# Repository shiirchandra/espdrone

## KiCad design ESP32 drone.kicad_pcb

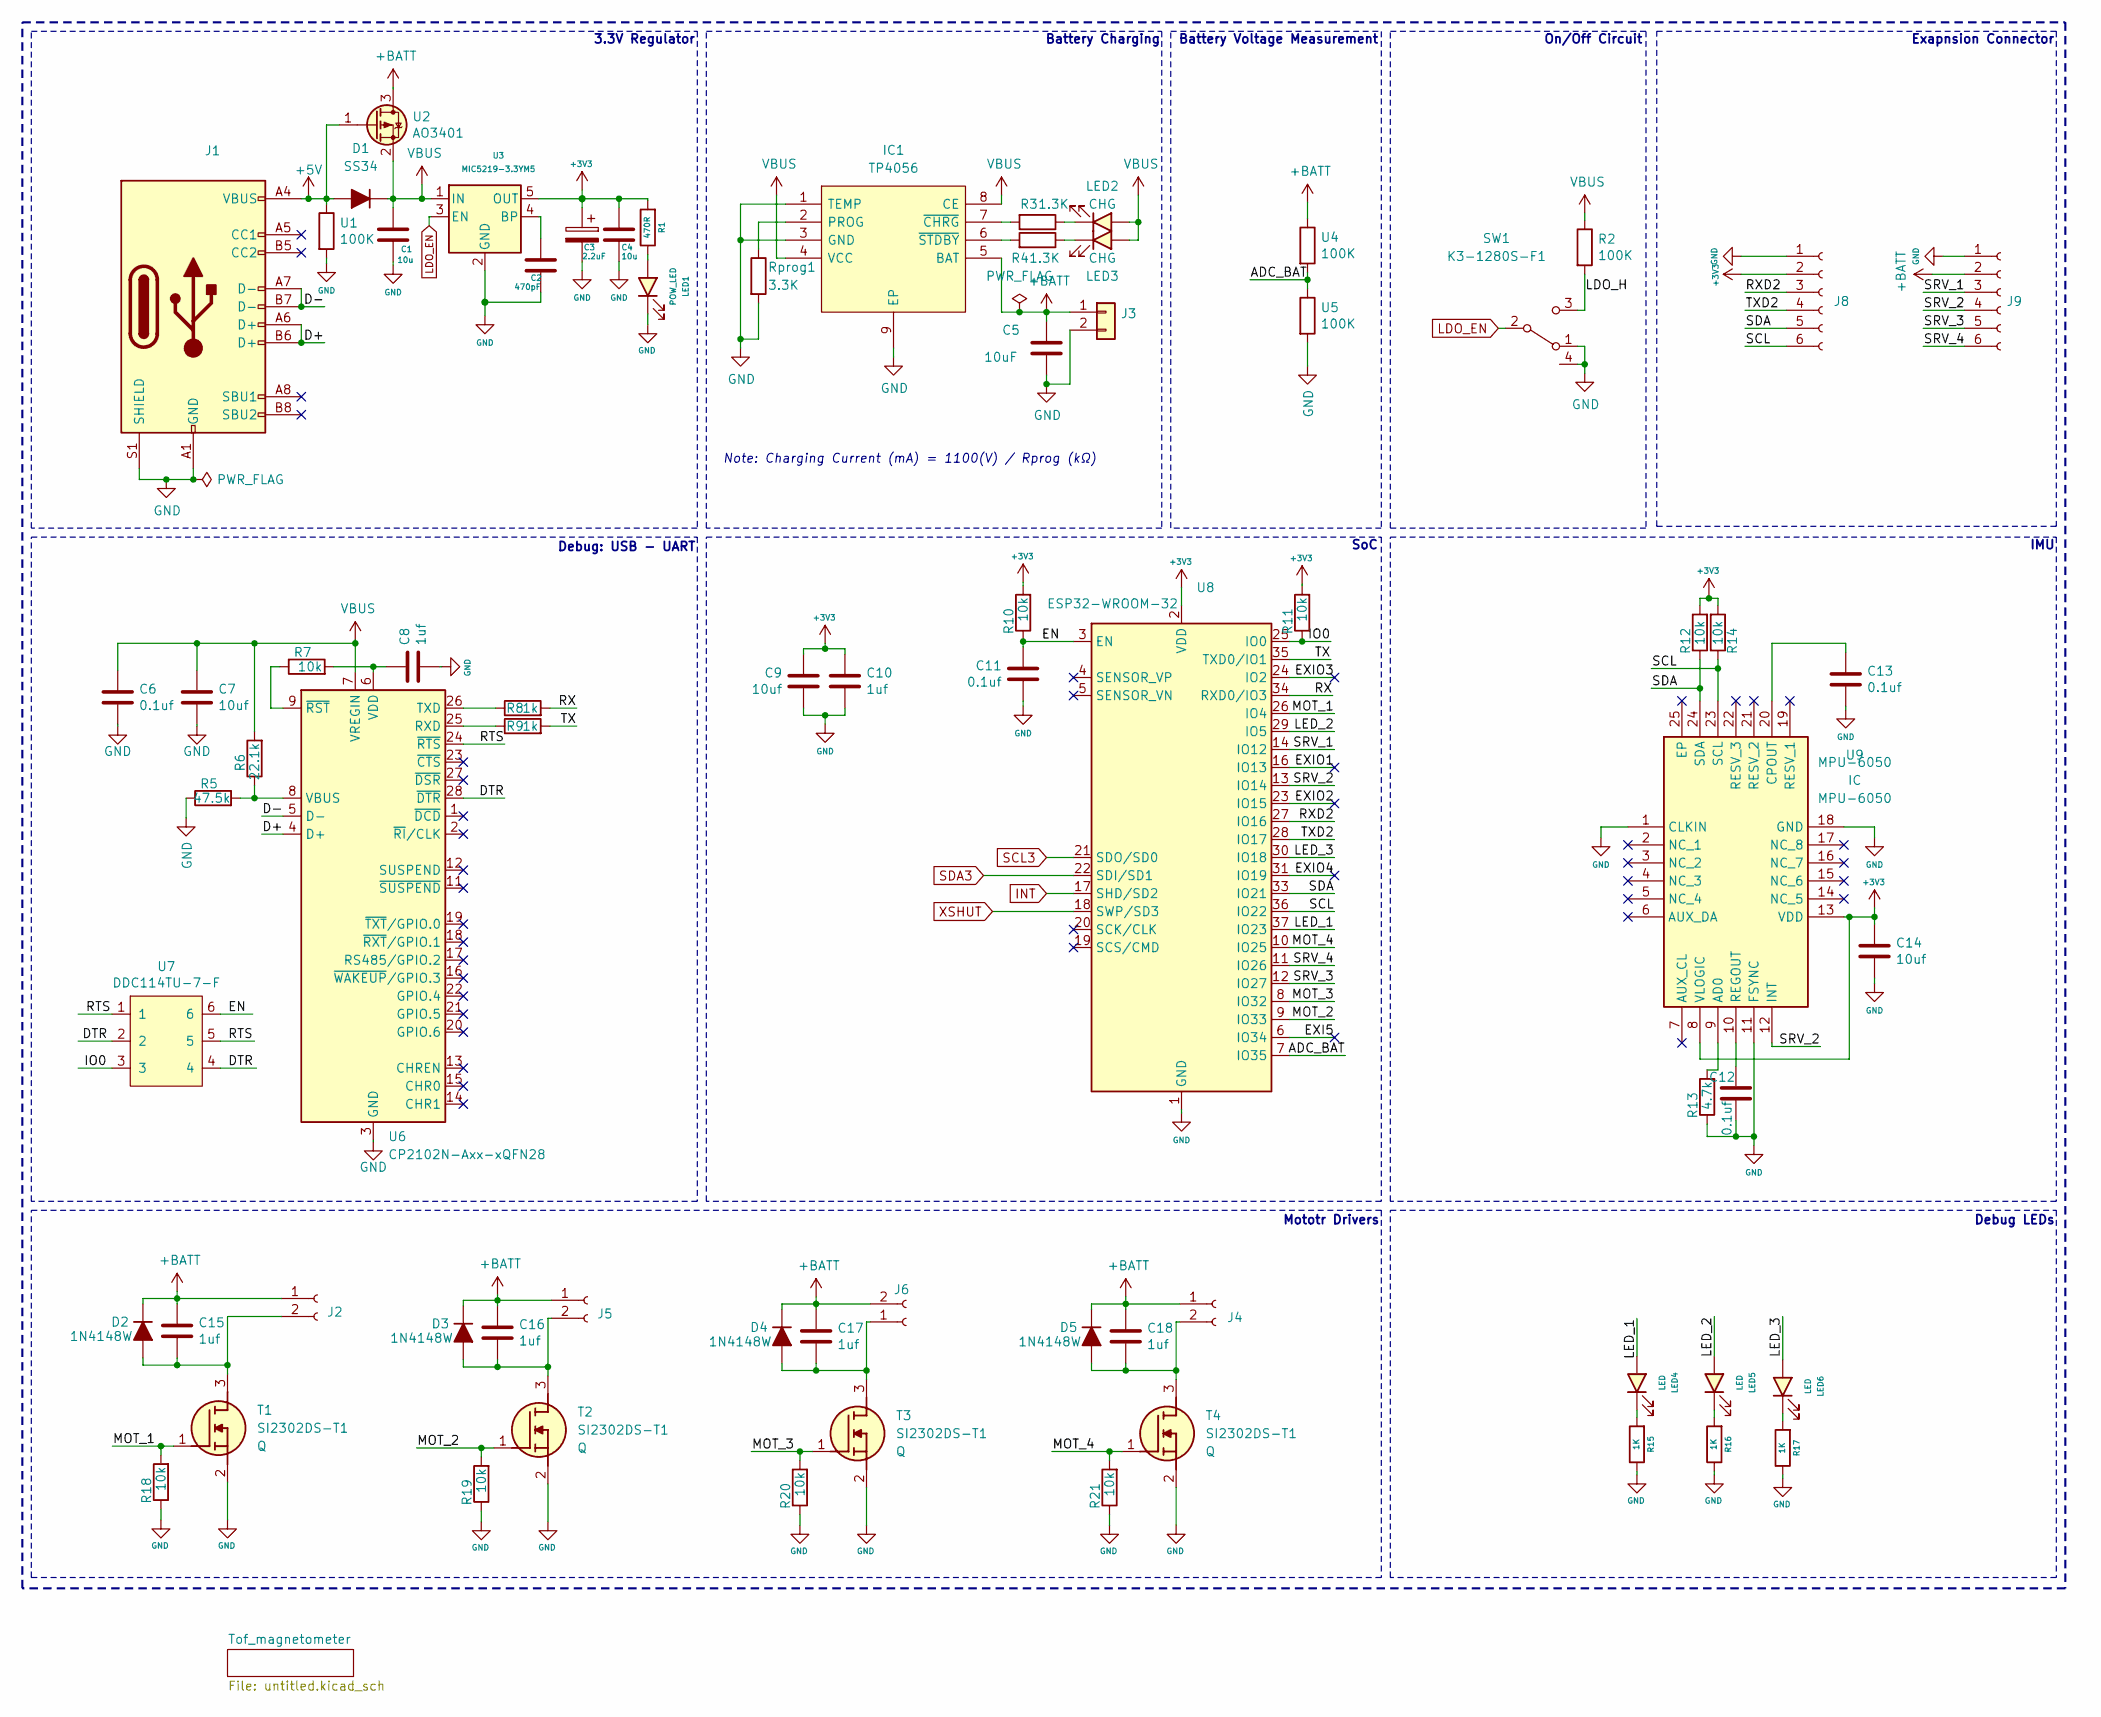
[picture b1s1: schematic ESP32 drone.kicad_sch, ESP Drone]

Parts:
C1, C4: 10u; C_0603_1608Metric
C2: 470pF; C_0603_1608Metric
C3: 2.2uF; C_0805_2012Metric
C5: 10uF; C_0603_1608Metric
C6, C11, C12, C13: 0.1uf; C_0603_1608Metric
C7, C9, C14: 10uf; C_0603_1608Metric
C8, C10, C15, C16, C17, C18: 1uf; C_0603_1608Metric
D1: SS34; D_SMA
D2, D3, D4, D5: 1N4148W; D_SOD-323
IC1: TP4056; SOIC-8-1EP_3.9x4.9mm_P1.27mm_EP2.29x3mm; Manufacturer_Part_Number TP4056-42-ESOP8
J1: USB_C_Receptacle_USB2.0; USB_C_Receptacle_HRO_TYPE-C-31-M-12
J2, J4, J5, J6: Conn_01x02_Female; JST_GH_SM02B-GHS-TB_1x02-1MP_P1.25mm_Horizontal
J3: B2B-PH-SM4-TB(LF)(SN); JST_PH_B2B-PH-SM4-TB_1x02-1MP_P2.00mm_Vertical
J8, J9: Conn_01x06_Female; PinHeader_1x06_P2.54mm_Vertical
LED1: POW_LED; LED_0603_1608Metric
LED2, LED3: CHG; LED_0603_1608Metric
LED4, LED5, LED6: LED; LED_0603_1608Metric
R1: 470R; R_0603_1608Metric
R2: 100K; R_0603_1608Metric
R3, R4: 1.3K; R_0603_1608Metric
R5: 47.5k; R_0603_1608Metric
R6: 22.1k; R_0603_1608Metric
R7, R10, R11, R12, R14, R18, R19, R20, R21: 10k; R_0603_1608Metric
R8, R9: 1k; R_0603_1608Metric
R13: 4.7k; R_0603_1608Metric
R15, R16, R17: 1K; R_0603_1608Metric
Rprog1: 3.3K; R_0603_1608Metric
SW1: K3-1280S-F1; slide switch spdt
T1, T2, T3, T4: SI2302DS-T1; SOT-23; Mouser Part Number 781-SI2302DS
U1, U4, U5: 100K; R_0603_1608Metric
U2: AO3401; SOT-23
U3: MIC5219-3.3YM5; SOT-23-5
U6: CP2102N-Axx-xQFN28; QFN-28-1EP_5x5mm_P0.5mm_EP3.35x3.35mm
U7: DDC114TU-7-F; SOT-363_SC-70-6
U8: ESP32-WROOM-32
U9: MPU-6050; MPU6050; Mouser Part Number 410-MPU-6050

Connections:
+3V3: C3.1, C4.1, C9.1, C10.1, C14.1, J8.2, R1.2, R10.2, R11.2, R12.2, R14.2, U3.5 (OUT), U8.2 (VDD), U9.8 (VLOGIC), U9.13 (VDD); also elsewhere on the board
+5V: D1.2 (A), J1.A4 (VBUS), J1.A9 (VBUS), J1.B4 (VBUS), J1.B9 (VBUS), U1.1, U2.1 (G)
+BATT: C5.1, C15.1, C16.1, C17.1, C18.1, D2.1 (K), D3.1 (K), D4.1 (K), D5.1 (K), IC1.5 (BAT), J2.1, J3.1, J4.1, J5.1, J6.2, J9.2, U2.3 (D), U4.1
/ADC_BAT: U4.2, U5.1, U8.7 (IO35)
/D+: J1.A6 (D+), J1.B6 (D+), U6.4 (D+)
/D-: J1.A7 (D-), J1.B7 (D-), U6.5 (D-)
/DTR: U6.28 (~DTR), U7.2, U7.4
/EN: C11.1, R10.1, U7.6, U8.3 (EN)
/EXI5: U8.6 (IO34)
/EXIO1: U8.16 (IO13)
/EXIO2: U8.23 (IO15)
/EXIO3: U8.24 (IO2)
/EXIO4: U8.31 (IO19)
/IO0: R11.1, U7.3, U8.25 (IO0)
/LDO_H: R2.2, SW1.3 (C)
/LED_1: LED4.2 (A), U8.37 (IO23)
/LED_2: LED5.2 (A), U8.29 (IO5)
/LED_3: LED6.2 (A), U8.30 (IO18)
/MOT_1: R18.2, T1.1 (G), U8.26 (IO4)
/MOT_2: R19.2, T2.1 (G), U8.9 (IO33)
/MOT_3: R20.2, T3.1 (G), U8.8 (IO32)
/MOT_4: R21.2, T4.1 (G), U8.10 (IO25)
/RTS: U6.24 (~RTS), U7.1, U7.5
/RX: R8.2, U8.34 (RXD0/IO3)
/RXD2: J8.3, U8.27 (IO16)
/SCL: J8.6, R14.1, U8.36 (IO22), U9.23 (SCL)
/SDA: J8.5, R12.1, U8.33 (IO21), U9.24 (SDA)
/SRV_1: J9.3, U8.14 (IO12)
/SRV_2: J9.4, U8.13 (IO14), U9.12 (INT)
/SRV_3: J9.5, U8.12 (IO27)
/SRV_4: J9.6, U8.11 (IO26)
/TX: R9.2, U8.35 (TXD0/IO1)
/TXD2: J8.4, U8.28 (IO17)
GND: C1.2, C2.2, C3.2, C4.2, C5.2, C6.2, C7.2, C8.2, C9.2, C10.2, C11.2, C12.2, C13.2, C14.2, IC1.1 (TEMP), IC1.3 (GND), IC1.9 (EP), J1.A1 (GND), J1.A12 (GND), J1.B1 (GND), J1.B12 (GND), J1.S1 (SHIELD), J3.2, J8.1, J9.1, LED1.1 (K), R5.1, R13.1, R15.1, R16.1, R17.1, R18.1, R19.1, R20.1, R21.1, Rprog1.2, SW1.1 (A), SW1.4, T1.2 (S), T2.2 (S), T3.2 (S), T4.2 (S), U1.2, U3.2 (GND), U5.2, U6.3 (GND), U6.29 (GND), U8.1 (GND), U8.15 (GND), U8.38 (GND), U8.39 (GND), U9.1 (CLKIN), U9.11 (FSYNC), U9.18 (GND); also elsewhere on the board
INT: U8.17 (SHD/SD2); also elsewhere on the board
LDO_EN: SW1.2 (B), U3.3 (EN)
unnamed: C15.2, D2.2 (A), J2.2, T1.3 (D)
unnamed: C16.2, D3.2 (A), J5.2, T2.3 (D)
unnamed: C17.2, D4.2 (A), J6.1, T3.3 (D)
unnamed: C18.2, D5.2 (A), J4.2, T4.3 (D)
unnamed: IC1.2 (PROG), Rprog1.1
unnamed: IC1.7 (~CHRG), R3.2
unnamed: IC1.6 (~STDBY), R4.2
unnamed: LED1.2 (A), R1.1
unnamed: LED2.1 (K), R3.1
unnamed: LED3.1 (K), R4.1
unnamed: LED4.1 (K), R15.2
unnamed: LED5.1 (K), R16.2
unnamed: LED6.1 (K), R17.2
unnamed: C2.1, U3.4 (BP)
unnamed: R9.1, U6.25 (RXD)
unnamed: R8.1, U6.26 (TXD)
unnamed: R5.2, R6.1, U6.8 (VBUS)
unnamed: C8.1, R7.2, U6.6 (VDD)
unnamed: R7.1, U6.9 (~RST)
unnamed: R13.2, U9.9 (AD0)
unnamed: C13.1, U9.20 (CPOUT)
unnamed: C12.1, U9.10 (REGOUT)
SCL3: U8.21 (SDO/SD0); also elsewhere on the board
SDA3: U8.22 (SDI/SD1); also elsewhere on the board
VBUS: C1.1, C6.1, C7.1, D1.1 (K), IC1.4 (VCC), IC1.8 (CE), LED2.2 (A), LED3.2 (A), R2.1, R6.2, U2.2 (S), U3.1 (IN), U6.7 (VREGIN)
XSHUT: U8.18 (SWP/SD3); also elsewhere on the board

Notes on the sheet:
SoC
Battery Voltage Measurement
IMU
Mototr Drivers
Battery Charging
Debug LEDs
Debug: USB - UART
Exapnsion Connector
3.3V Regulator
Note: Charging Current (mA) = 1100(V) / Rprog (kΩ)
On/Off Circuit

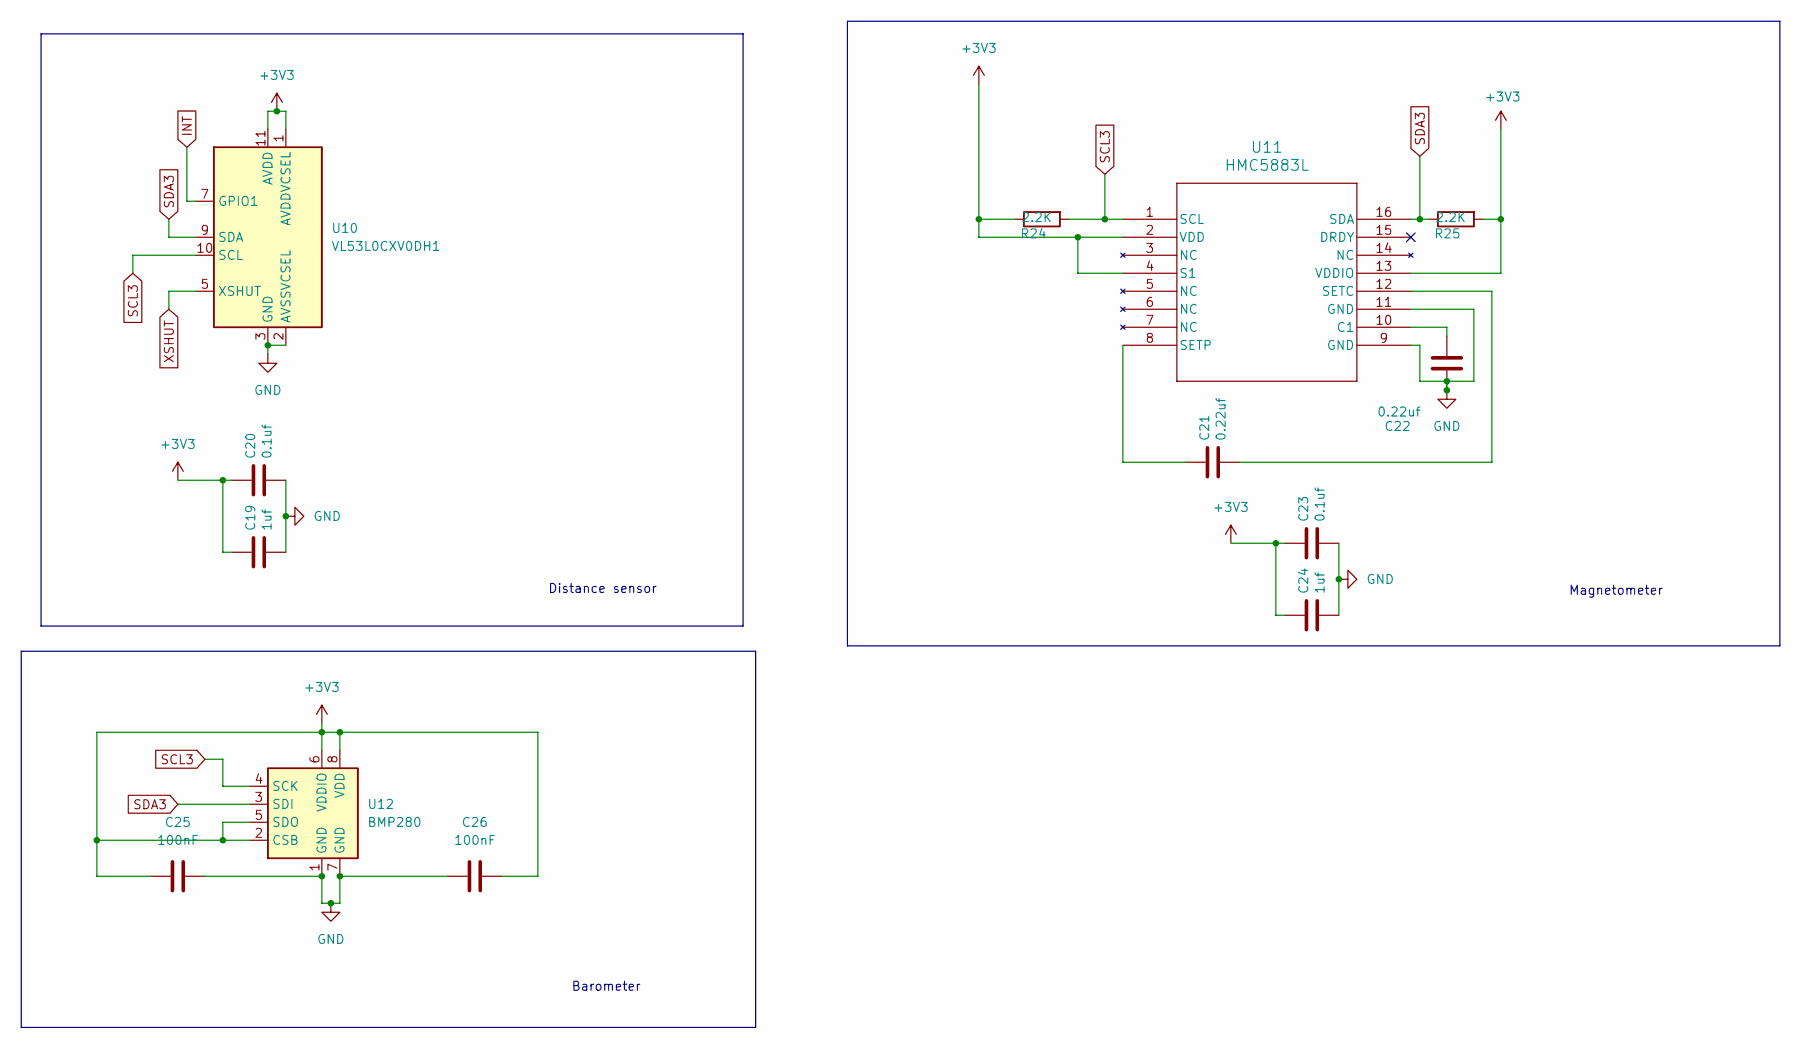
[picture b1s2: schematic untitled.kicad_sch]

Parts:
C19, C24: 1uf; C_0603_1608Metric
C20, C23: 0.1uf; C_0603_1608Metric
C21, C22: 0.22uf; C_0603_1608Metric
C25, C26: 100nF; C_0603_1608Metric
R24, R25: 2.2K; R_0603_1608Metric
U10: VL53L0CXV0DH1; ST_VL53L1x
U11: HMC5883L; LPCC16_HNW
U12: BMP280; Bosch_LGA-8_2x2.5mm_P0.65mm_ClockwisePinNumbering

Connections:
+3V3: C19.1, C20.1, C23.1, C24.1, C25.1, C26.2, R24.1, R25.2, U10.1 (AVDDVCSEL), U10.11 (AVDD), U11.2 (VDD), U11.4 (S1), U11.13 (VDDIO), U12.2 (CSB), U12.5 (SDO), U12.6 (VDDIO), U12.8 (VDD); also elsewhere on the board
GND: C19.2, C20.2, C22.2, C23.2, C24.2, C25.2, C26.1, U10.2 (AVSSVCSEL), U10.3 (GND), U10.4 (GND), U10.6 (GND), U10.12 (GND), U11.9 (GND), U11.11 (GND), U12.1 (GND), U12.7 (GND); also elsewhere on the board
INT: U10.7 (GPIO1); also elsewhere on the board
unnamed: C22.1, U11.10 (C1)
unnamed: C21.2, U11.12 (SETC)
unnamed: C21.1, U11.8 (SETP)
SCL3: R24.2, U10.10 (SCL), U11.1 (SCL), U12.4 (SCK); also elsewhere on the board
SDA3: R25.1, U10.9 (SDA), U11.16 (SDA), U12.3 (SDI); also elsewhere on the board
XSHUT: U10.5 (XSHUT); also elsewhere on the board

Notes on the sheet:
Magnetometer
Distance sensor
Barometer

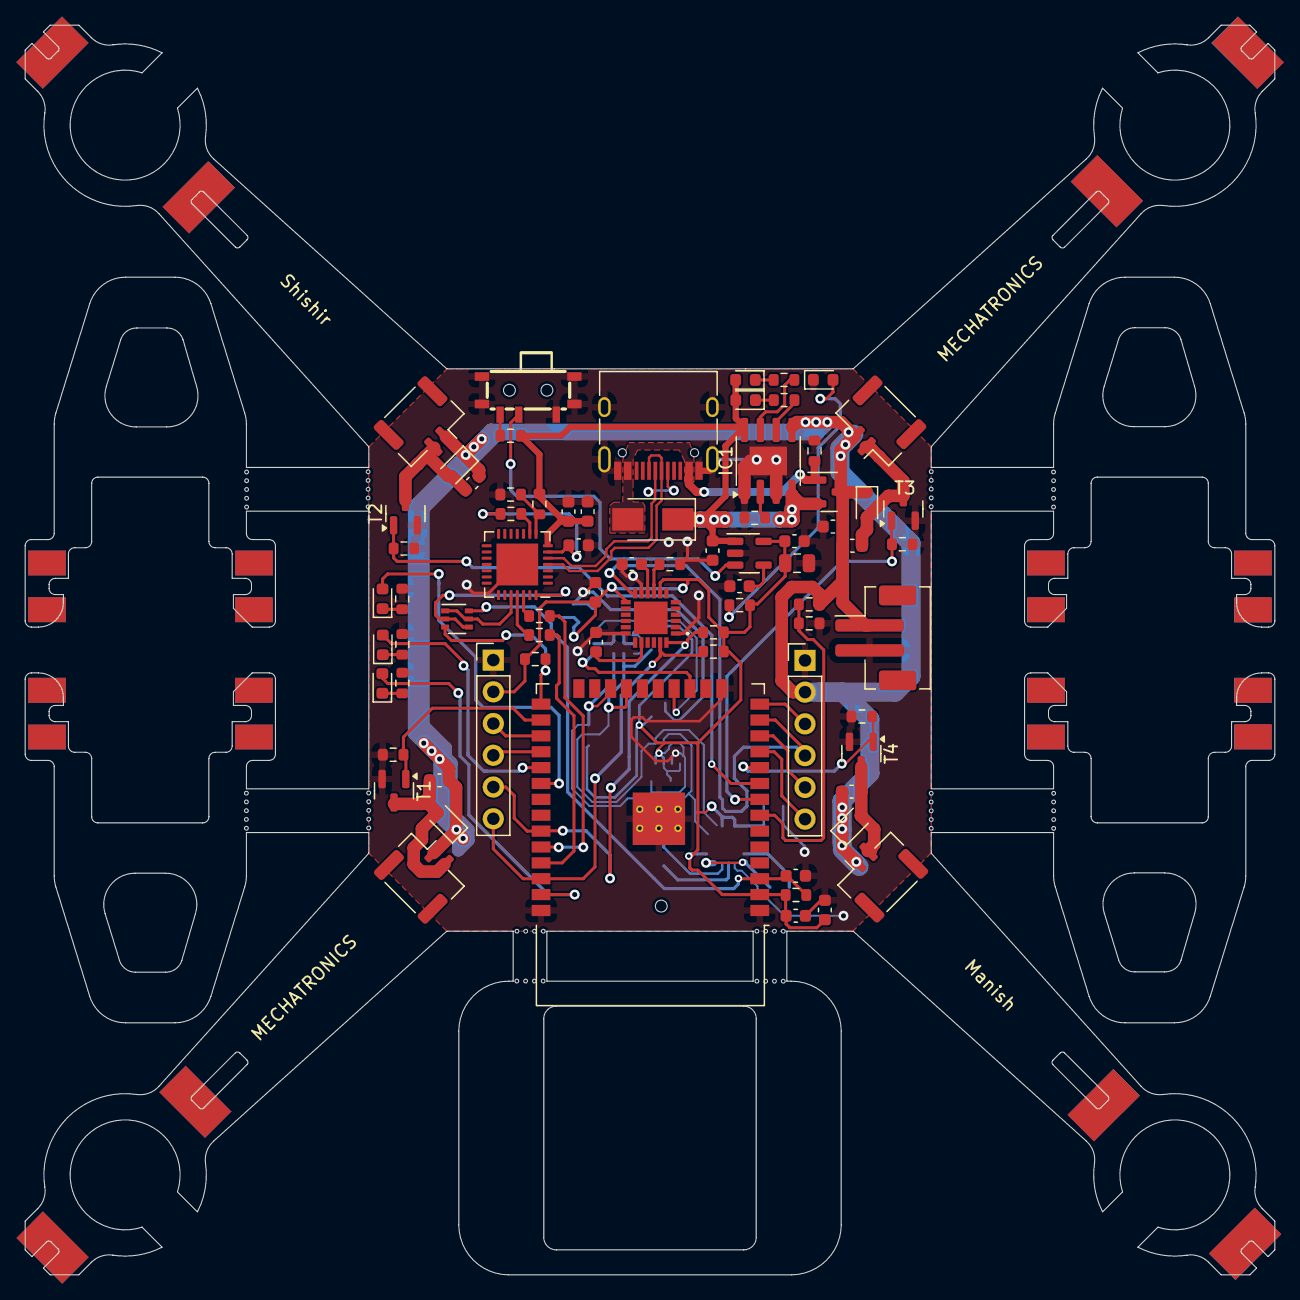
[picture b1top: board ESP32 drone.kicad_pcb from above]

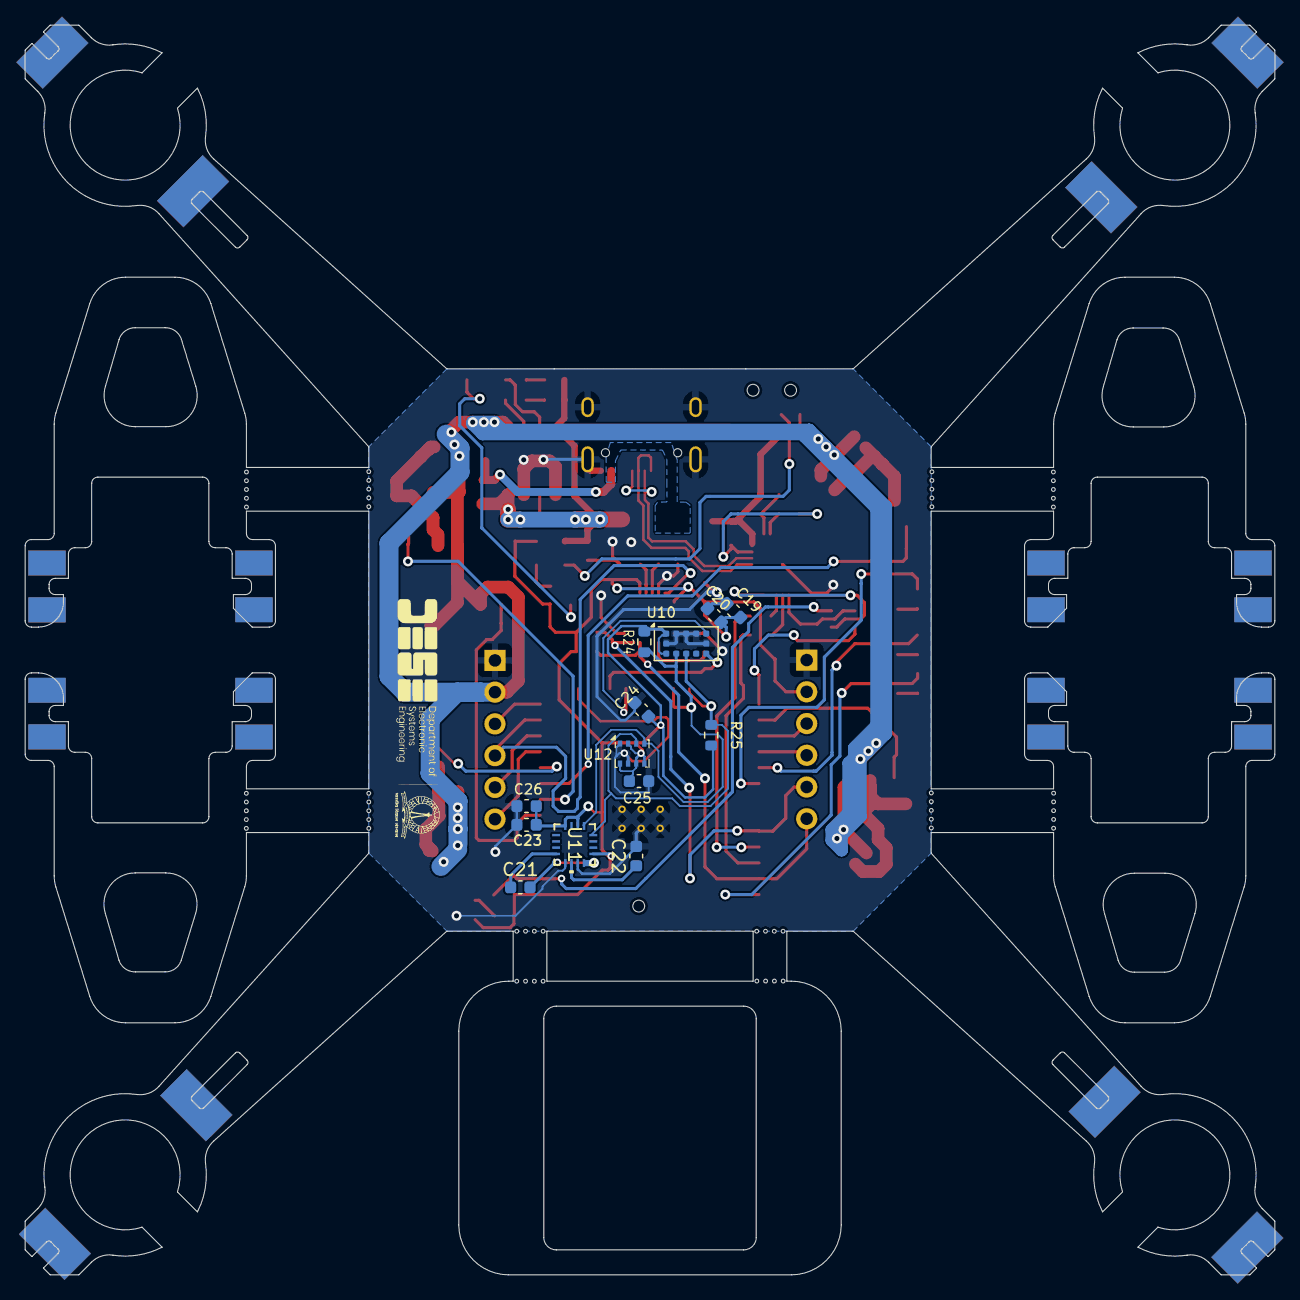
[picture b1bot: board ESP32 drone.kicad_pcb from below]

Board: 2 copper layers, 100.0 x 100.0 mm, 87 parts (13 on the bottom side), 60 nets.

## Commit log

2024-12-30 Initial commit of Kicad for Drone project
